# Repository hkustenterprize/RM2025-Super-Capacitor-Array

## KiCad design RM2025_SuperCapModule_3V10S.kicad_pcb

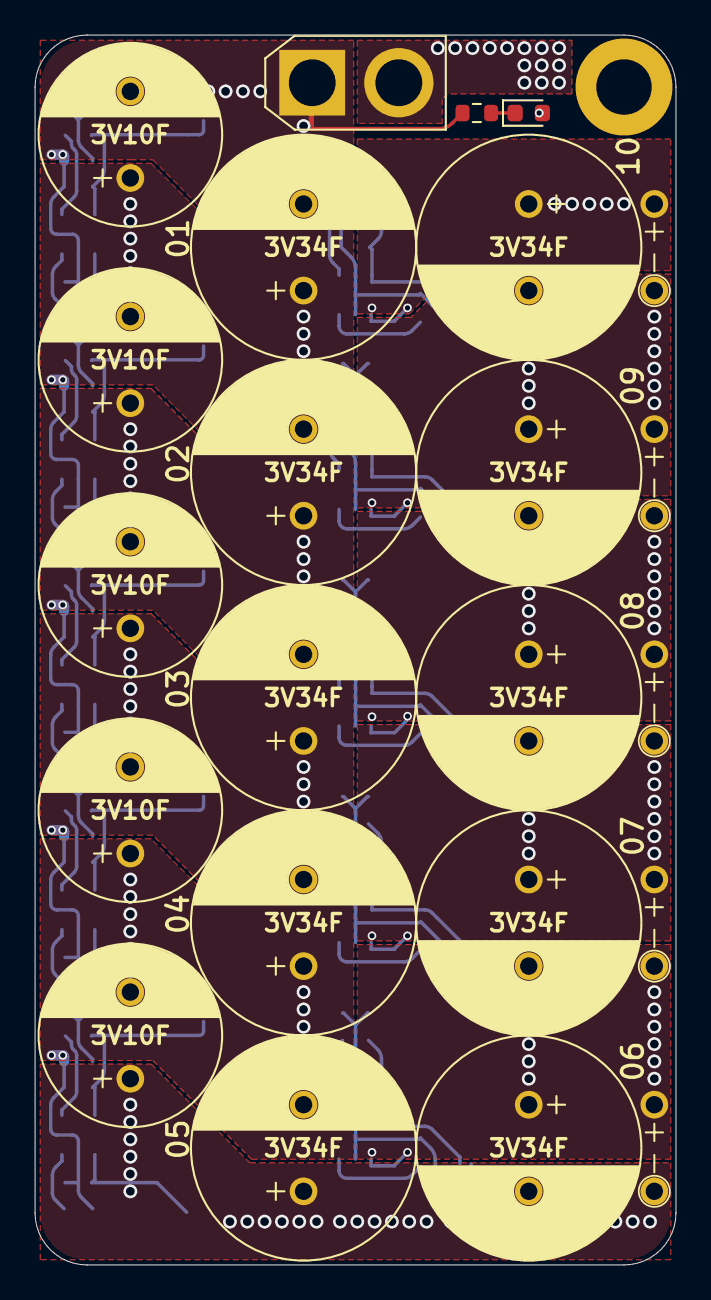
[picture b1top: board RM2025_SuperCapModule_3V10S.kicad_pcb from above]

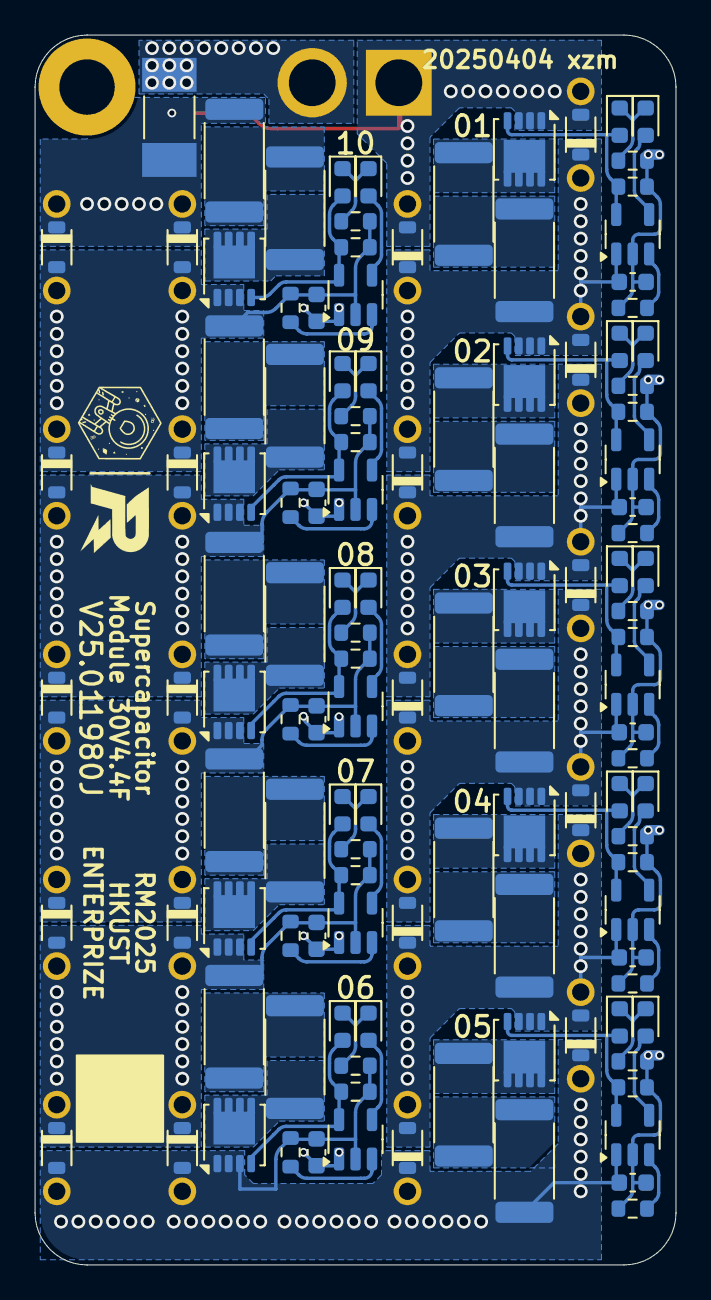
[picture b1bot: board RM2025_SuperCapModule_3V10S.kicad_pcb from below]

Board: 2 copper layers, 37.0 x 71.0 mm, 145 parts (121 on the bottom side), 73 nets.

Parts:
C1, C3, C5, C7, C9, C24, C26, C28, C30, C32: 3V 34F; TV1245-3R0346-R
C2, C4, C6, C8, C10: 3V 10F; TV1030-3R0106-R
C13, C14, C15, C16, C17, C18, C19, C20, C21, C22: 100n; C_0603_1608Metric
C25, C27, C29, C31, C33: 3V 10F; TV1030-3R0106-R-Hor
D1, D4, D6, D8, D10, D16, D18, D20, D22, D24: R; LED_0603_1608Metric
D2, D11, D12, D15, D26, D27, D28, D29, D30, D31, D32, D33, D34, D35, D36, D37, D38, D39, D40, D41: PMEG4010BEA; D_SOD-323_HS
D3, D5, D7, D9, D14, D17, D19, D21, D23, D25: Y; LED_0603_1608Metric
D13: LED; LED_0603_1608Metric
F1: Fuse; Fuse_Littelfuse-NANO2-451_453
H4: MountingHole_Pad; MountingHole_3.2mm_M3_DIN965_Pad
J1: Conn_01x02; AMASS_XT30U-F_1x02_P5.0mm_Vertical
Q1, Q2, Q3, Q5, Q6, Q7, Q8, Q9, Q10, Q11: AP2045Q; MOS_PDFN_3.3x3.3mm
R1, R6, R13, R18, R19, R24, R25, R30, R31, R36, R37, R42, R43, R48, R49, R54, R55, R60, R61, R66: 1k; R_0603_1608Metric
R3, R5, R15, R17, R21, R23, R27, R29, R33, R35, R39, R41, R45, R47, R51, R53, R57, R59, R63, R65: 0R3; R_2512_6332Metric
R4, R16, R22, R28, R34, R40, R46, R52, R58, R64: 330R; R_0603_1608Metric
R67: 100k; R_0603_1608Metric
U1, U3, U4, U5, U6, U7, U8, U9, U10, U11: BW6103; SOT-23-5

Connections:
CAP_1P: C7.2, C8.2, C9.1, C10.1, C16.2, C17.1, D30.2 (A), D31.1 (K), D40.2 (A), D41.1 (K), Q5.1 (S), Q5.2 (S), Q5.3 (S), R25.2, R28.2, R30.2, R33.1, U5.2 (GND), U6.1 (VDD)
CAP_2P: C5.2, C6.2, C7.1, C8.1, C15.2, C16.1, D29.2 (A), D30.1 (K), D39.2 (A), D40.1 (K), Q3.1 (S), Q3.2 (S), Q3.3 (S), R19.2, R22.2, R24.2, R27.1, U4.2 (GND), U5.1 (VDD)
CAP_3P: C3.2, C4.2, C5.1, C6.1, C14.2, C15.1, D28.2 (A), D29.1 (K), D38.2 (A), D39.1 (K), Q2.1 (S), Q2.2 (S), Q2.3 (S), R13.2, R16.2, R18.2, R21.1, U3.2 (GND), U4.1 (VDD)
CAP_4P: C1.2, C2.2, C3.1, C4.1, C13.2, C14.1, D27.2 (A), D28.1 (K), D37.2 (A), D38.1 (K), Q1.1 (S), Q1.2 (S), Q1.3 (S), R1.2, R4.2, R6.2, R15.1, U1.2 (GND), U3.1 (VDD)
CAP_5P: C1.1, C2.1, C13.1, C22.2, C32.2, C33.2, D26.2 (A), D27.1 (K), D36.2 (A), D37.1 (K), Q11.1 (S), Q11.2 (S), Q11.3 (S), R3.1, R61.2, R64.2, R66.2, U1.1 (VDD), U11.2 (GND)
CAP_6P: C21.2, C22.1, C30.2, C31.2, C32.1, C33.1, D15.2 (A), D26.1 (K), D35.2 (A), D36.1 (K), Q10.1 (S), Q10.2 (S), Q10.3 (S), R55.2, R58.2, R60.2, R63.1, U10.2 (GND), U11.1 (VDD)
CAP_7P: C20.2, C21.1, C28.2, C29.2, C30.1, C31.1, D12.2 (A), D15.1 (K), D34.2 (A), D35.1 (K), Q9.1 (S), Q9.2 (S), Q9.3 (S), R49.2, R52.2, R54.2, R57.1, U9.2 (GND), U10.1 (VDD)
CAP_8P: C19.2, C20.1, C26.2, C27.2, C28.1, C29.1, D11.2 (A), D12.1 (K), D33.2 (A), D34.1 (K), Q8.1 (S), Q8.2 (S), Q8.3 (S), R43.2, R46.2, R48.2, R51.1, U8.2 (GND), U9.1 (VDD)
CAP_9P: C18.2, C19.1, C24.2, C25.2, C26.1, C27.1, D2.2 (A), D11.1 (K), D32.2 (A), D33.1 (K), Q7.1 (S), Q7.2 (S), Q7.3 (S), R37.2, R40.2, R42.2, R45.1, U7.2 (GND), U8.1 (VDD)
CAP_10P: C18.1, C24.1, C25.1, D2.1 (K), D13.2 (A), D32.1 (K), F1.1, R39.1, U7.1 (VDD)
GND: C9.2, C10.2, C17.2, D31.2 (A), D41.2 (A), J1.1, Q6.1 (S), Q6.2 (S), Q6.3 (S), R31.2, R34.2, R36.2, R67.2, U6.2 (GND)
unnamed: D1.2 (A), U1.4 (LED)
unnamed: D1.1 (K), D3.1 (K), R4.1
unnamed: D3.2 (A), Q1.4 (G), R6.1, U1.5 (IOUT)
unnamed: D4.2 (A), U3.4 (LED)
unnamed: D4.1 (K), D5.1 (K), R16.1
unnamed: D5.2 (A), Q2.4 (G), R18.1, U3.5 (IOUT)
unnamed: D6.2 (A), U4.4 (LED)
unnamed: D6.1 (K), D7.1 (K), R22.1
unnamed: D7.2 (A), Q3.4 (G), R24.1, U4.5 (IOUT)
unnamed: D8.2 (A), U5.4 (LED)
unnamed: D8.1 (K), D9.1 (K), R28.1
unnamed: D9.2 (A), Q5.4 (G), R30.1, U5.5 (IOUT)
unnamed: D10.2 (A), U6.4 (LED)
unnamed: D10.1 (K), D14.1 (K), R34.1
unnamed: D13.1 (K), R67.1
unnamed: D14.2 (A), Q6.4 (G), R36.1, U6.5 (IOUT)
unnamed: D16.2 (A), U7.4 (LED)
unnamed: D16.1 (K), D17.1 (K), R40.1
unnamed: D17.2 (A), Q7.4 (G), R42.1, U7.5 (IOUT)
unnamed: D18.2 (A), U8.4 (LED)
unnamed: D18.1 (K), D19.1 (K), R46.1
unnamed: D19.2 (A), Q8.4 (G), R48.1, U8.5 (IOUT)
unnamed: D20.2 (A), U9.4 (LED)
unnamed: D20.1 (K), D21.1 (K), R52.1
unnamed: D21.2 (A), Q9.4 (G), R54.1, U9.5 (IOUT)
unnamed: D22.2 (A), U10.4 (LED)
unnamed: D22.1 (K), D23.1 (K), R58.1
unnamed: D23.2 (A), Q10.4 (G), R60.1, U10.5 (IOUT)
unnamed: D24.2 (A), U11.4 (LED)
unnamed: D24.1 (K), D25.1 (K), R64.1
unnamed: D25.2 (A), Q11.4 (G), R66.1, U11.5 (IOUT)
unnamed: F1.2, J1.2
unnamed: Q1.5 (D), R5.2
unnamed: Q2.5 (D), R17.2
unnamed: Q3.5 (D), R23.2
unnamed: Q5.5 (D), R29.2
unnamed: Q6.5 (D), R35.2
unnamed: Q7.5 (D), R41.2
unnamed: Q8.5 (D), R47.2
unnamed: Q9.5 (D), R53.2
unnamed: Q10.5 (D), R59.2
unnamed: Q11.5 (D), R65.2
unnamed: R3.2, R5.1
unnamed: R15.2, R17.1
unnamed: R21.2, R23.1
unnamed: R27.2, R29.1
unnamed: R33.2, R35.1
unnamed: R39.2, R41.1
unnamed: R45.2, R47.1
unnamed: R51.2, R53.1
unnamed: R57.2, R59.1
unnamed: R63.2, R65.1
unnamed: R1.1, U1.3 (SEL)
unnamed: R13.1, U3.3 (SEL)
unnamed: R19.1, U4.3 (SEL)
unnamed: R25.1, U5.3 (SEL)
unnamed: R31.1, U6.3 (SEL)
unnamed: R37.1, U7.3 (SEL)
unnamed: R43.1, U8.3 (SEL)
unnamed: R49.1, U9.3 (SEL)
unnamed: R55.1, U10.3 (SEL)
unnamed: R61.1, U11.3 (SEL)

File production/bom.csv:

Designator,Footprint,Quantity,Value,LCSC Part #
"C1, C24, C26, C28, C3, C30, C32, C5, C7, C9",TV1245-3R0346-R,10,3V 34F,
"C10, C2, C4, C6, C8",TV1030-3R0106-R,5,3V 10F,
"C13, C14, C15, C16, C17, C18, C19, C20, C21, C22",0603,10,100n,
"C25, C27, C29, C31, C33",TV1030-3R0106-R-Hor,5,3V 10F,
"D1, D10, D16, D18, D20, D22, D24, D4, D6, D8",0603,10,R,
"D11, D12, D15, D2, D26, D27, D28, D29, D30, D31, D32, D33, D34, D35, D36, D37, D38, D39, D40, D41",D_SOD-323_HS,20,PMEG4010BEA,
D13,0603,1,LED,
"D14, D17, D19, D21, D23, D25, D3, D5, D7, D9",0603,10,Y,
F1,Fuse_Littelfuse-NANO2-451_453,1,Fuse,
J1,AMASS_XT30U-F_1x02_P5.0mm_Vertical,1,Conn_01x02,
"Q1, Q10, Q11, Q2, Q3, Q5, Q6, Q7, Q8, Q9",MOS_PDFN_3.3x3.3mm,10,AP2045Q,
"R1, R13, R18, R19, R24, R25, R30, R31, R36, R37, R42, R43, R48, R49, R54, R55, R6, R60, R61, R66",0603,20,1k,
"R15, R17, R21, R23, R27, R29, R3, R33, R35, R39, R41, R45, R47, R5, R51, R53, R57, R59, R63, R65",2512,20,0R3,
"R16, R22, R28, R34, R4, R40, R46, R52, R58, R64",0603,10,330R,
R67,0603,1,100k,
"U1, U10, U11, U3, U4, U5, U6, U7, U8, U9",SOT-23-5,10,BW6103,

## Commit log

2025-08-01 工程文件
2025-08-01 外壳文件
